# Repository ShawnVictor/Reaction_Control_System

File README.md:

# Reaction_Control_System
This is a repository containing all of the design documents relating to my Reaction Control System (RCS).

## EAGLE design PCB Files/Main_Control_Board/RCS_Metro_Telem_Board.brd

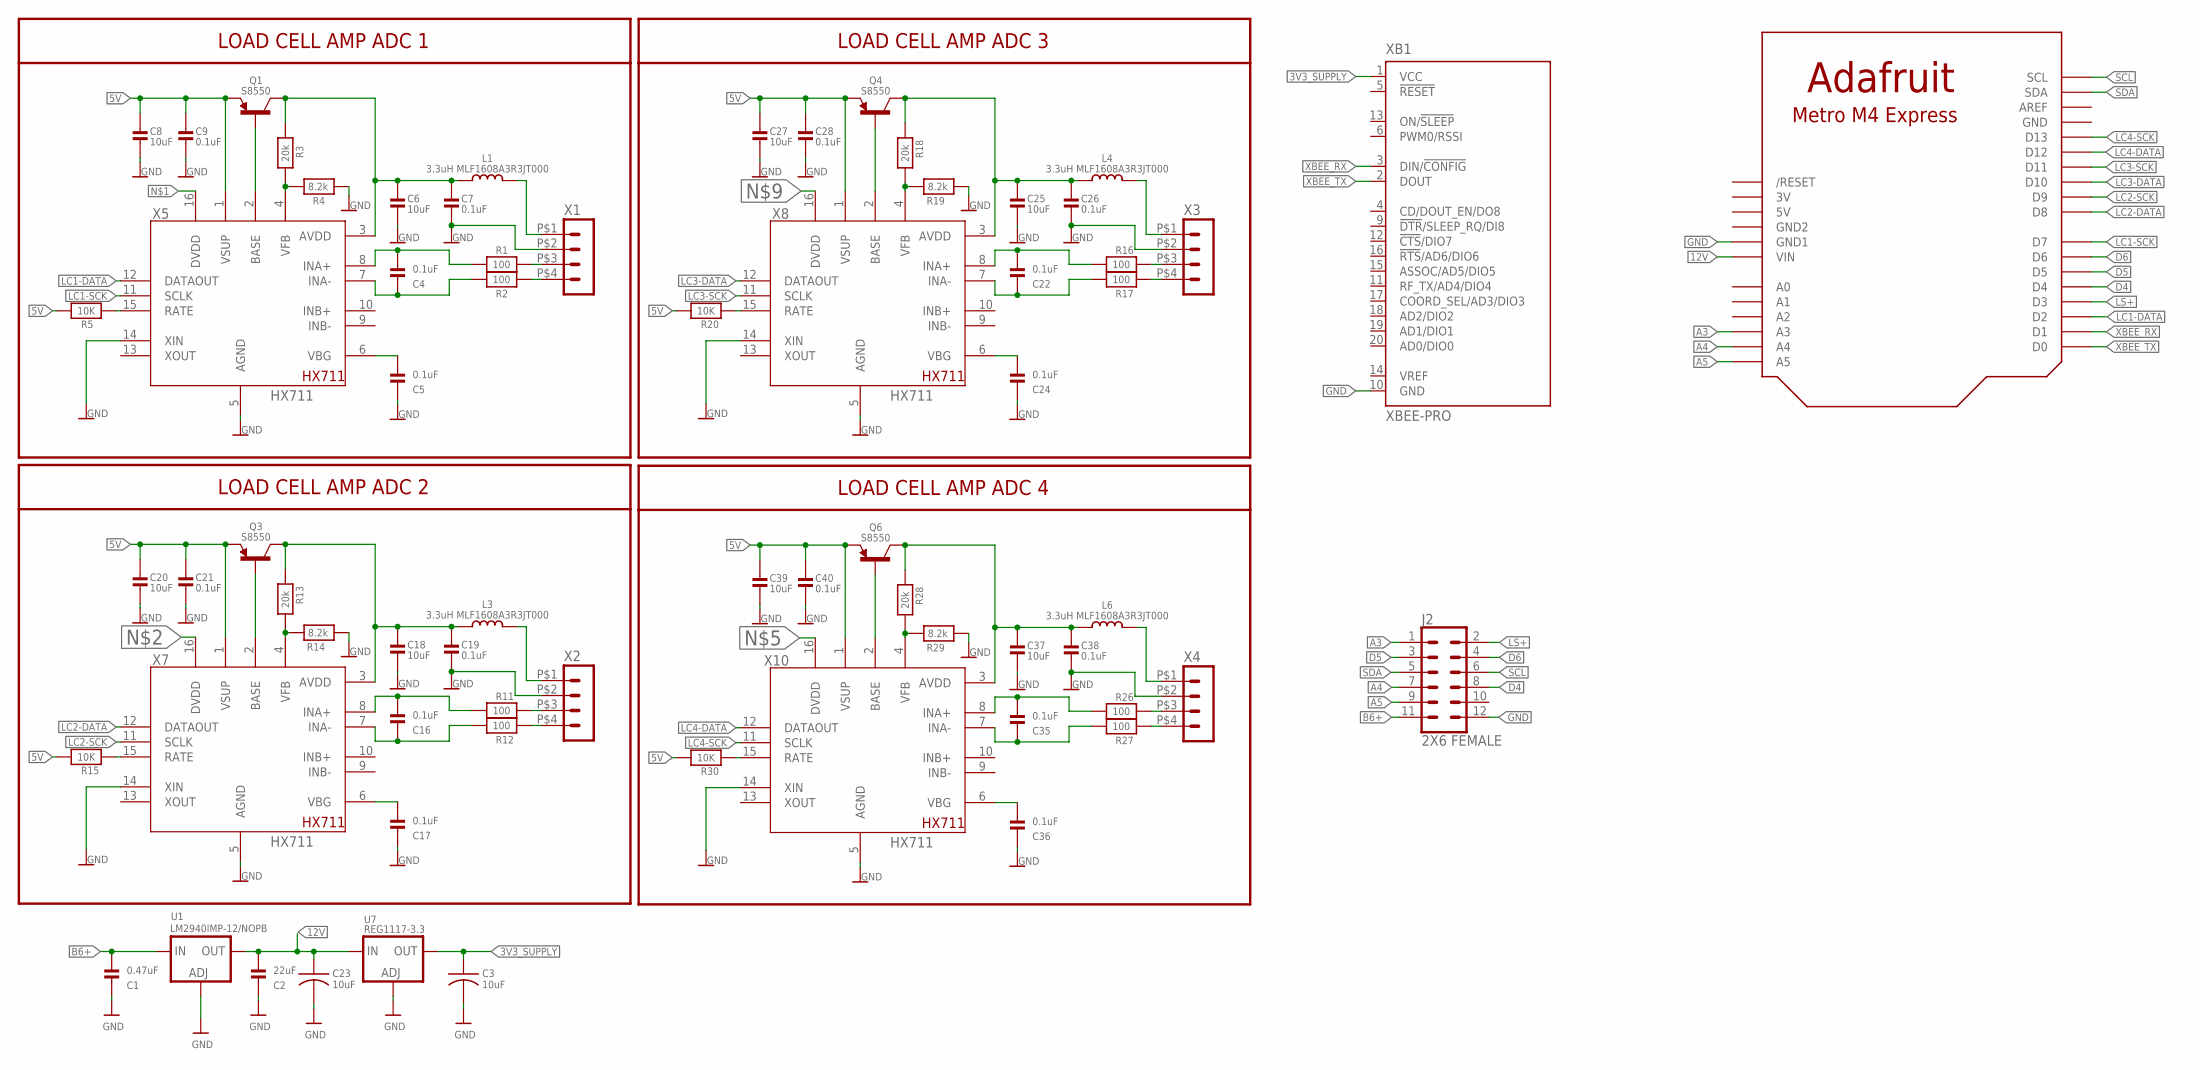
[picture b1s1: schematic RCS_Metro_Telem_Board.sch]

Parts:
C1: 0.47uF; 0603@1
C2: 22uF; 0603@1
C3, C23: 10uF; C0603
C4, C5, C7, C9, C16, C17, C19, C21, C22, C24, C26, C28, C35, C36, C38, C40: 0.1uF; 0603@1
C6, C8, C18, C20, C25, C27, C37, C39: 10uF; 0603@1
J2: 2X6 FEMALE; 2X6
L1, L3, L4, L6: 3.3uH MLF1608A3R3JT000; 0603-NO
Q1, Q3, Q4, Q6: S8550; SOT23-WIDE
R1, R2, R11, R12, R16, R17, R26, R27: 100; 0603@1
R3, R13, R18, R28: 20k; 0603@1
R4, R14, R19, R29: 8.2k; 0603@1
R5, R15, R20, R30: 10K; 0603@1
U1: LM2940IMP-12/NOPB; SOT223-R
U7: REG1117-3.3; SOT223-R
U$1: ADAFRUIT_METRO_M4_EXPRESS
X1, X2, X3, X4: HEADER_POS4_43650-0415; 43650-0415
X5, X7, X8, X10: HX711; SO16
XB1: XBEE-PRO

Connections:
3V: U$1.3V
3V3_SUPPLY: C3.1, U7.2 (OUT), XB1.1 (VCC)
5V: C8.2, C9.2, C20.2, C21.2, C27.2, C28.2, C39.2, C40.2, Q1.2 (E), Q3.2 (E), Q4.2 (E), Q6.2 (E), R5.1, R15.1, R20.1, R30.1, U$1.5V, X5.1 (VSUP), X7.1 (VSUP), X8.1 (VSUP), X10.1 (VSUP)
12V: C2.2, C23.1, U1.2 (OUT), U7.3 (IN), U$1.VIN
A3: J2.1, U$1.A3
A4: J2.7, U$1.A4
A5: J2.9, U$1.A5
B6+: C1.2, J2.11, U1.3 (IN)
D4: J2.8, U$1.D4
D5: J2.3, U$1.D5
D6: J2.4, U$1.D6
GND: C1.1, C2.1, C3.2, C5.1, C6.1, C7.1, C8.1, C9.1, C17.1, C18.1, C19.1, C20.1, C21.1, C23.2, C24.1, C25.1, C26.1, C27.1, C28.1, C36.1, C37.1, C38.1, C39.1, C40.1, J2.12, R4.1, R14.1, R19.1, R29.1, U1.1 (ADJ), U7.1 (ADJ), U$1.GND, U$1.GND1, X1.P$2 (2), X2.P$2 (2), X3.P$2 (2), X4.P$2 (2), X5.5 (AGND), X5.14 (XIN), X7.5 (AGND), X7.14 (XIN), X8.5 (AGND), X8.14 (XIN), X10.5 (AGND), X10.14 (XIN), XB1.10 (GND)
GND2: U$1.GND2
LC1-DATA: U$1.D2, X5.12 (DATAOUT)
LC1-SCK: U$1.D7, X5.11 (SCLK)
LC2-DATA: U$1.D8, X7.12 (DATAOUT)
LC2-SCK: U$1.D9, X7.11 (SCLK)
LC3-DATA: U$1.D10, X8.12 (DATAOUT)
LC3-SCK: U$1.D11, X8.11 (SCLK)
LC4-DATA: U$1.D12, X10.12 (DATAOUT)
LC4-SCK: U$1.D13, X10.11 (SCLK)
LS+: J2.2, U$1.D3
unnamed: R1.2, X1.P$3 (3)
unnamed: R2.2, X1.P$4 (4)
unnamed: C4.1, R2.1, X5.7 (INA-)
unnamed: C4.2, R1.1, X5.8 (INA+)
unnamed: C5.2, X5.6 (VBG)
unnamed: L1.2, X1.P$1 (1)
unnamed: R3.1, R4.2, X5.4 (VFB)
unnamed: Q1.1 (B), X5.2 (BASE)
unnamed: C6.2, C7.2, L1.1, Q1.3 (C), R3.2, X5.3 (AVDD)
unnamed: R5.2, X5.15 (RATE)
unnamed: R11.2, X2.P$3 (3)
unnamed: R12.2, X2.P$4 (4)
unnamed: C16.1, R12.1, X7.7 (INA-)
unnamed: C16.2, R11.1, X7.8 (INA+)
unnamed: C17.2, X7.6 (VBG)
unnamed: L3.2, X2.P$1 (1)
unnamed: R13.1, R14.2, X7.4 (VFB)
unnamed: Q3.1 (B), X7.2 (BASE)
unnamed: C18.2, C19.2, L3.1, Q3.3 (C), R13.2, X7.3 (AVDD)
unnamed: R15.2, X7.15 (RATE)
unnamed: R16.2, X3.P$3 (3)
unnamed: R17.2, X3.P$4 (4)
unnamed: C22.1, R17.1, X8.7 (INA-)
unnamed: C22.2, R16.1, X8.8 (INA+)
unnamed: C24.2, X8.6 (VBG)
unnamed: L4.2, X3.P$1 (1)
unnamed: R18.1, R19.2, X8.4 (VFB)
unnamed: Q4.1 (B), X8.2 (BASE)
unnamed: C25.2, C26.2, L4.1, Q4.3 (C), R18.2, X8.3 (AVDD)
unnamed: R20.2, X8.15 (RATE)
unnamed: R26.2, X4.P$3 (3)
unnamed: R27.2, X4.P$4 (4)
unnamed: C35.1, R27.1, X10.7 (INA-)
unnamed: C35.2, R26.1, X10.8 (INA+)
unnamed: C36.2, X10.6 (VBG)
unnamed: L6.2, X4.P$1 (1)
unnamed: R28.1, R29.2, X10.4 (VFB)
unnamed: Q6.1 (B), X10.2 (BASE)
unnamed: C37.2, C38.2, L6.1, Q6.3 (C), R28.2, X10.3 (AVDD)
unnamed: R30.2, X10.15 (RATE)
SCL: J2.6, U$1.SCL
SDA: J2.5, U$1.SDA
XBEE_RX: U$1.D1, XB1.3 (DIN/!CONFIG)
XBEE_TX: U$1.D0, XB1.2 (DOUT)

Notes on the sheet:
LOAD CELL AMP ADC 1
LOAD CELL AMP ADC 2
LOAD CELL AMP ADC 3
LOAD CELL AMP ADC 4

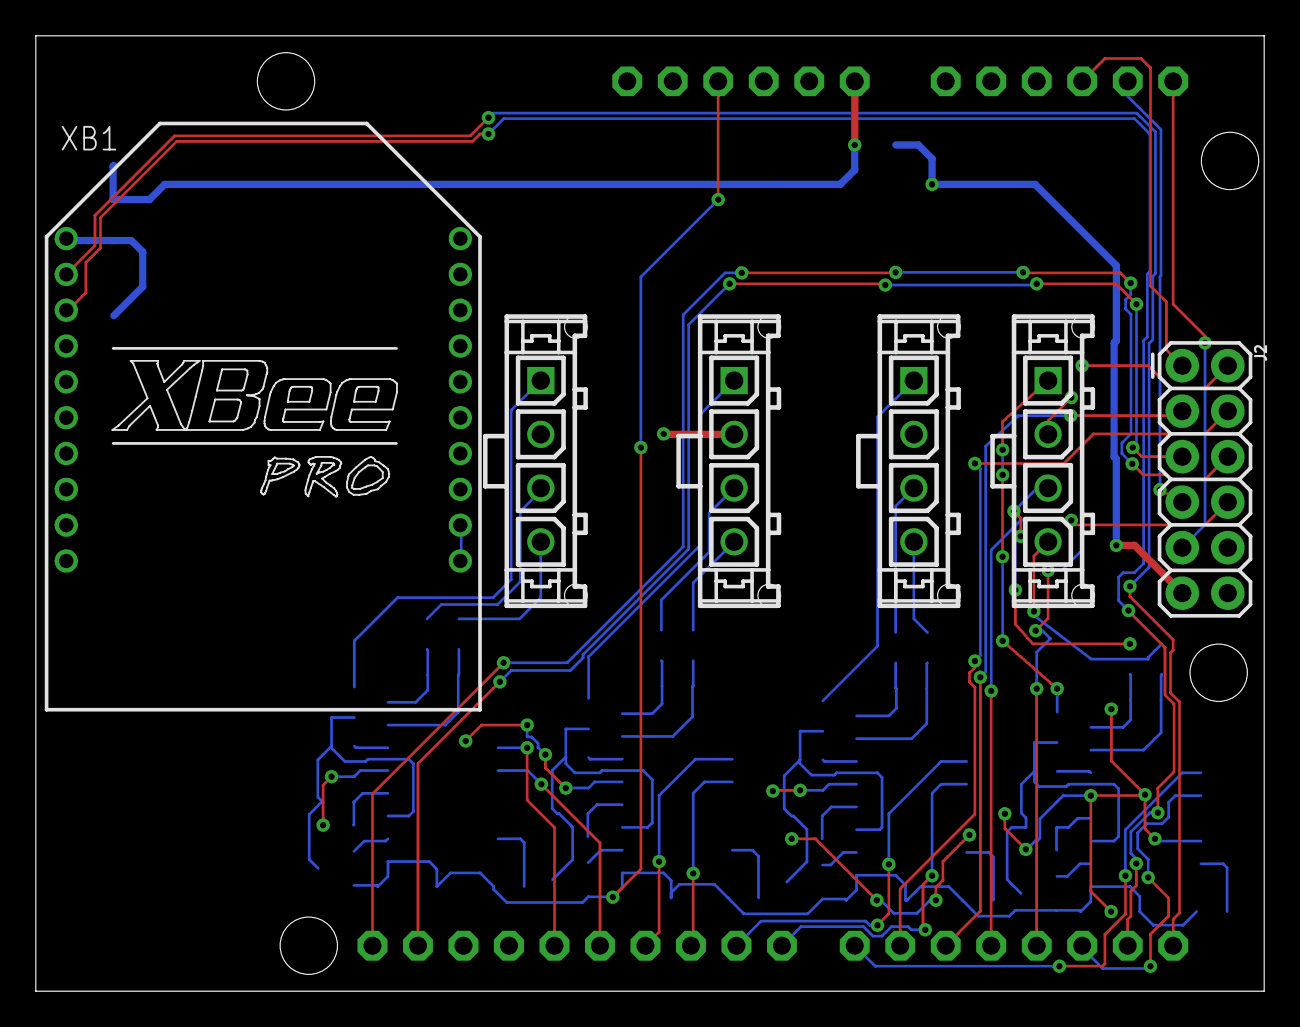
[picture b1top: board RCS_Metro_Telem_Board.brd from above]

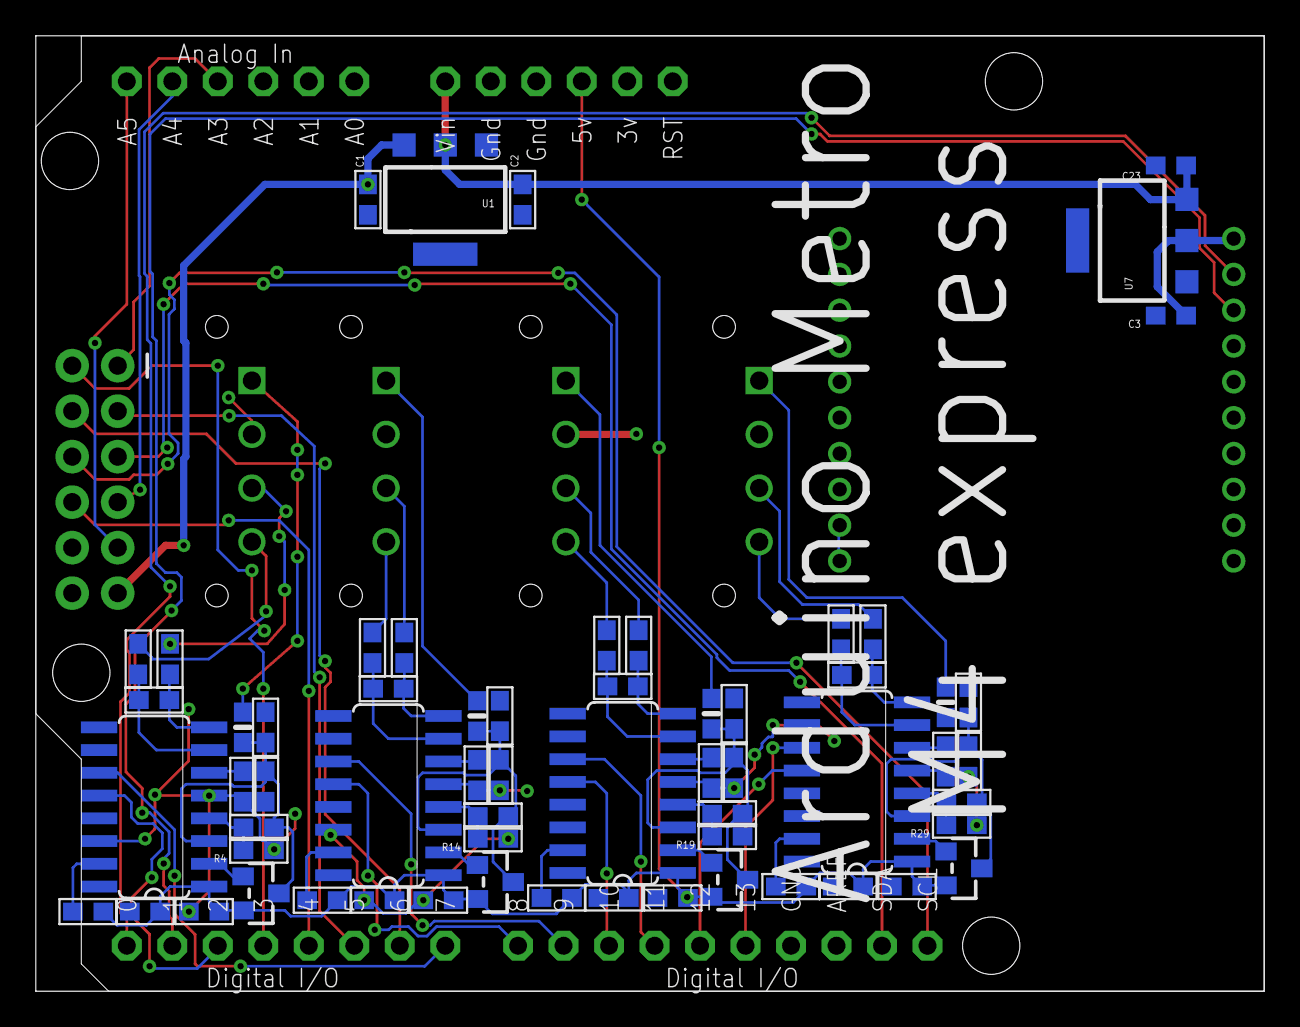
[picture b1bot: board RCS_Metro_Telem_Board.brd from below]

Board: 2 copper layers, 68.6 x 53.3 mm, 69 parts (63 on the bottom side), 64 nets.

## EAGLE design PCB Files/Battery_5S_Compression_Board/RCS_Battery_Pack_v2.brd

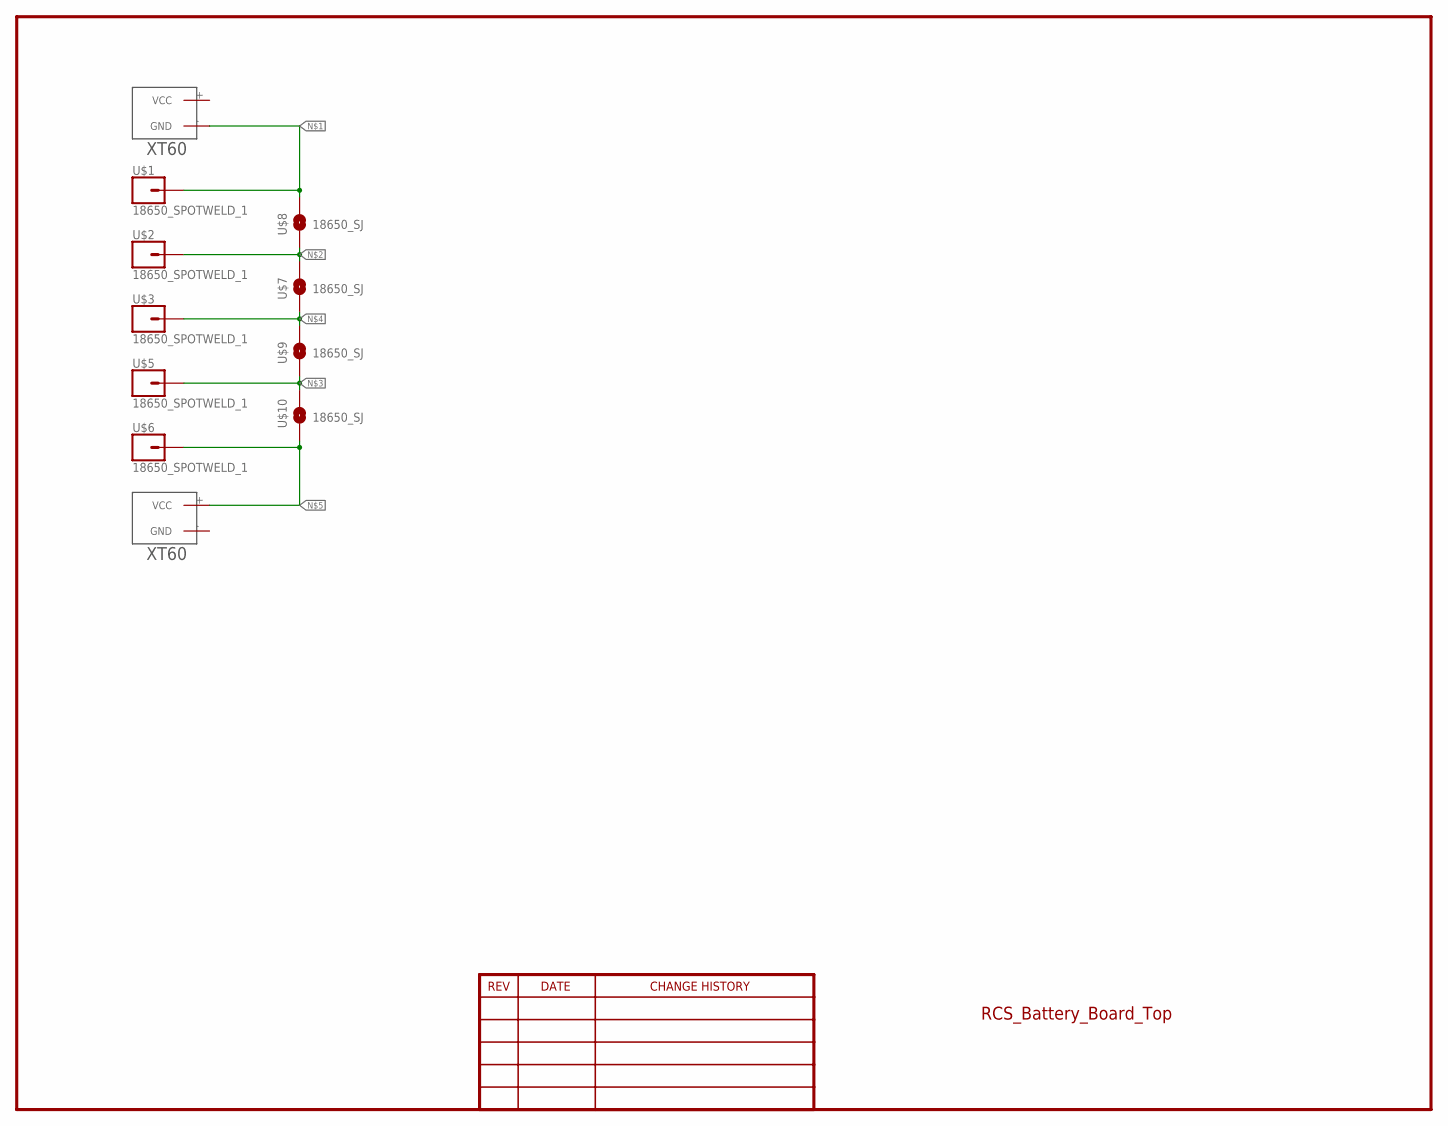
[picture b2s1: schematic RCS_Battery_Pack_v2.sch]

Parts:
U$1, U$2, U$3, U$5, U$6: 18650_SPOTWELD_1
U$4, U$11: XT60
U$7, U$8, U$9, U$10: 18650_SJ; SJ_2S-NO

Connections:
unnamed: U$1.1, U$4.- (GND), U$8.2
unnamed: U$2.1, U$7.2, U$8.1
unnamed: U$5.1, U$9.1, U$10.2
unnamed: U$3.1, U$7.1, U$9.2
unnamed: U$6.1, U$10.1, U$11.+ (VCC)

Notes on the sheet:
RCS_Battery_Board_Top

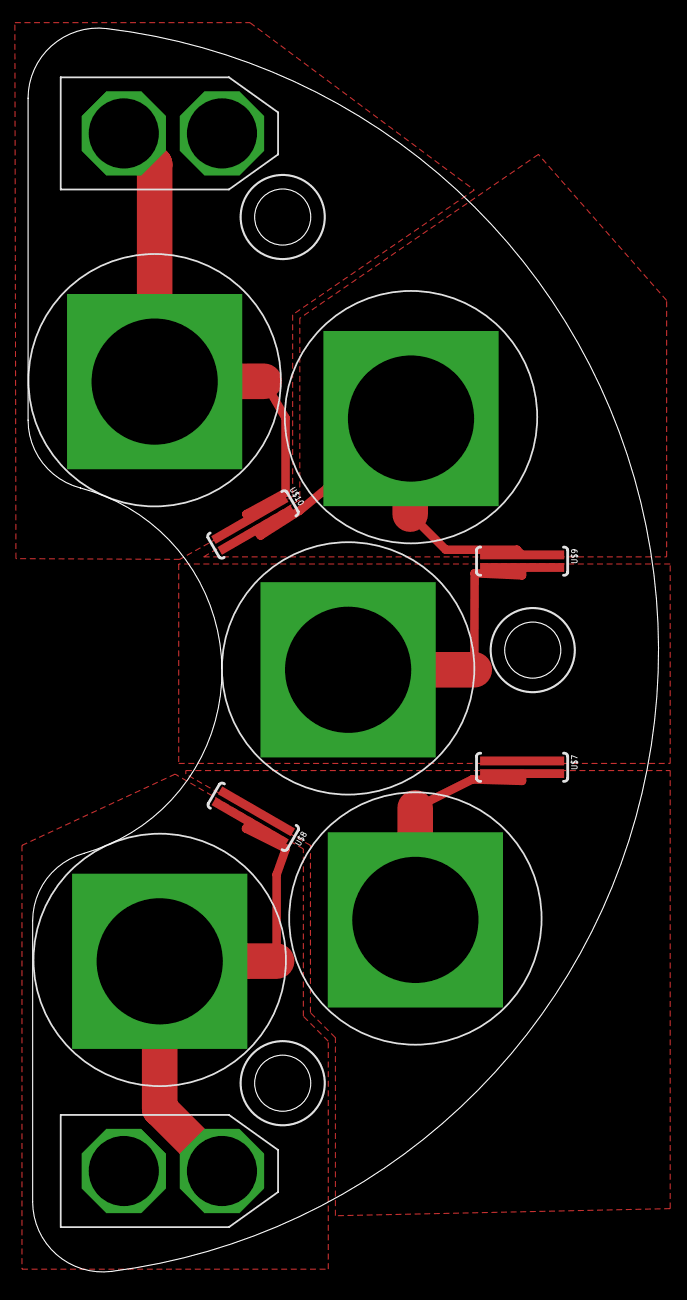
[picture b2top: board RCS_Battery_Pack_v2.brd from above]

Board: 2 copper layers, 45.0 x 88.7 mm, 11 parts (0 on the bottom side), 5 nets.

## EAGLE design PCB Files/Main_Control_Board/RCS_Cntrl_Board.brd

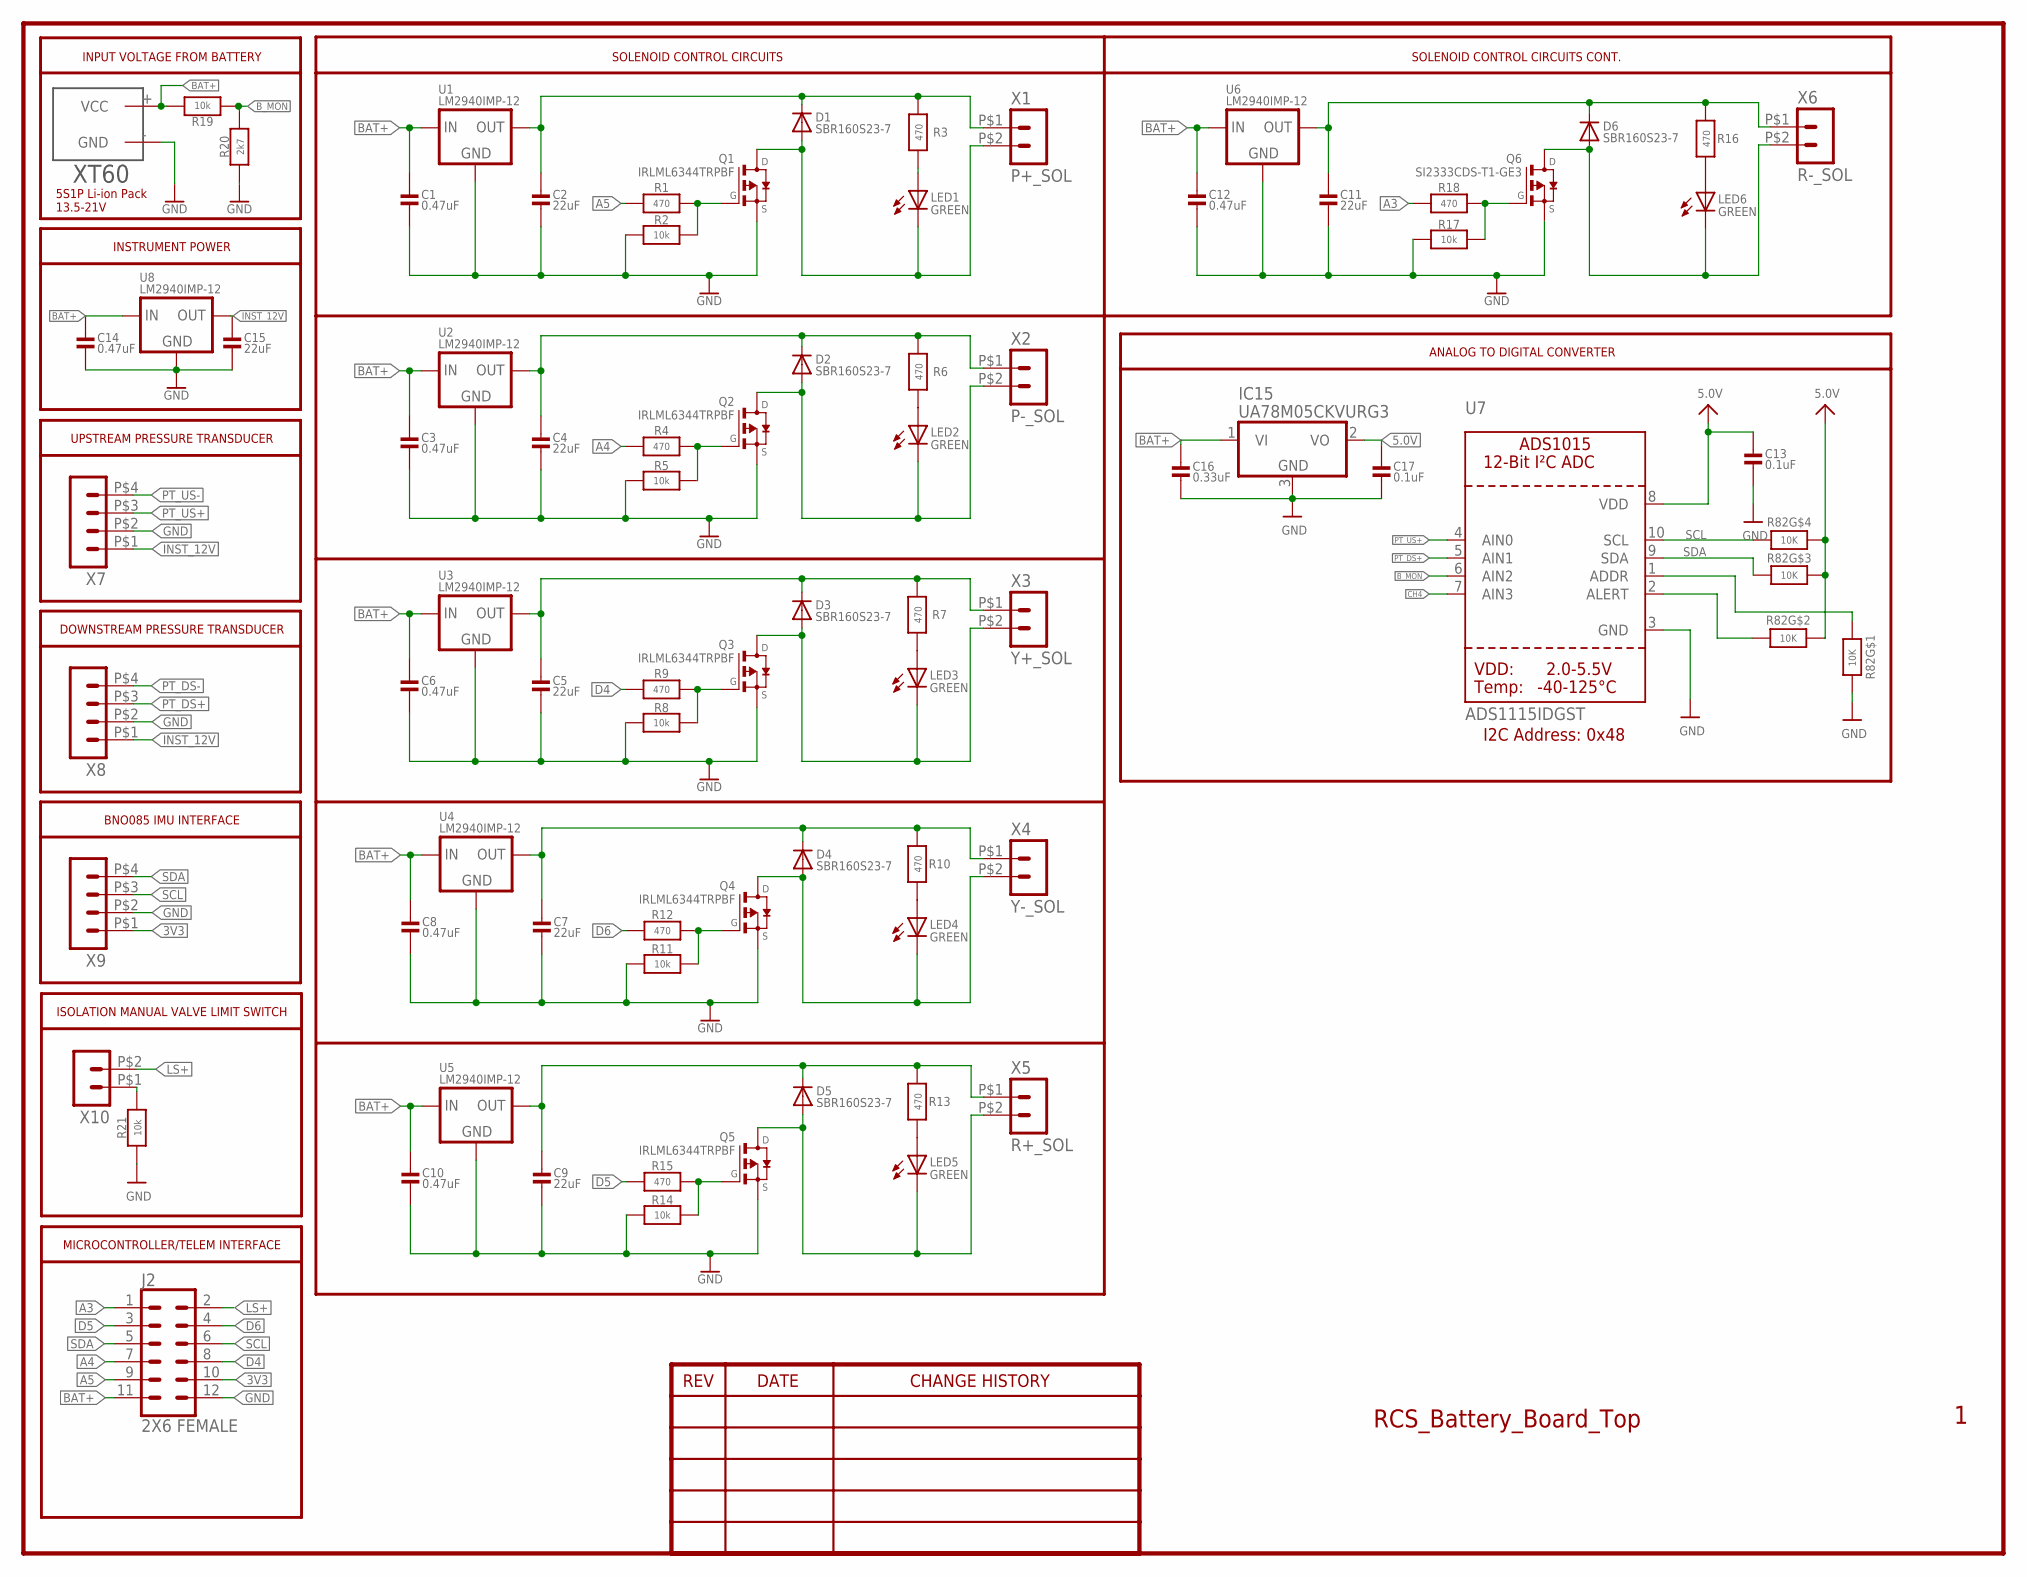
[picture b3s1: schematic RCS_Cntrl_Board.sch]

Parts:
C1, C3, C6, C8, C10, C12, C14: 0.47uF; 0603
C2, C4, C5, C7, C9, C11, C15: 22uF; 0603
C13, C17: 0.1uF; 0603
C16: 0.33uF; 0603
D1, D2, D3, D4, D5, D6: SBR160S23-7; SOT23-R
IC15: UA78M05CKVURG3; TO252
J2: 2X6 FEMALE; 2X6
LED1, LED2, LED3, LED4, LED5, LED6: GREEN; CHIPLED_0603
Q1, Q2, Q3, Q4, Q5: IRLML6344TRPBF; TRANSISTOR-FET_SOT23
Q6: SI2333CDS-T1-GE3; TRANSISTOR-FET_SOT23
R1, R3, R4, R6, R7, R9, R10, R12, R13, R15, R16, R18: 470; 0603-NO
R2, R5, R8, R11, R14, R17, R19, R21: 10k; 0603-NO
R20: 2k7; 0603-NO
R82: 10K; RESPACK_4X0603
U1, U2, U3, U4, U5, U6, U8: LM2940IMP-12; SOT223-R
U7: ADS1115IDGST; MSOP10
U$4: XT60
X1: P+_SOL; 44914-0201
X2: P-_SOL; 44914-0201
X3: Y+_SOL; 44914-0201
X4: Y-_SOL; 44914-0201
X5: R+_SOL; 44914-0201
X6: R-_SOL; 44914-0201
X7, X8, X9: HEADER_POS4_43650-0415; 43650-0415
X10: HEADER_POS2_43650-0215; 43650-0215

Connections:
3V3: J2.10, X9.P$1 (1)
5.0V: C13.2, C17.2, IC15.2 (VO), R82.5 (2), R82.6 (2), R82.7 (2), U7.8 (VDD)
A3: J2.1, R18.1
A4: J2.7, R4.1
A5: J2.9, R1.1
BAT+: C1.2, C3.2, C6.2, C8.2, C10.2, C12.2, C14.2, C16.2, IC15.1 (VI), J2.11, R19.2, U1.1 (IN), U2.1 (IN), U3.1 (IN), U4.1 (IN), U5.1 (IN), U6.1 (IN), U8.1 (IN), U$4.+ (VCC)
B_MON: R19.1, R20.2, U7.6 (AIN2)
CH4: U7.7 (AIN3)
D4: J2.8, R9.1
D5: J2.3, R15.1
D6: J2.4, R12.1
GND: C1.1, C2.1, C3.1, C4.1, C5.1, C6.1, C7.1, C8.1, C9.1, C10.1, C11.1, C12.1, C13.1, C14.1, C15.1, C16.1, C17.1, IC15.3 (GND), J2.12, Q1.2 (S), Q2.2 (S), Q3.2 (S), Q4.2 (S), Q5.2 (S), Q6.2 (S), R2.1, R5.1, R8.1, R11.1, R14.1, R17.1, R20.1, R21.1, R82.8 (2), U1.2 (GND), U2.2 (GND), U3.2 (GND), U4.2 (GND), U5.2 (GND), U6.2 (GND), U7.3 (GND), U8.2 (GND), U$4.- (GND), X7.P$2 (2), X8.P$2 (2), X9.P$2 (2)
INST_12V: C15.2, U8.3 (OUT), X7.P$1 (1), X8.P$1 (1)
LS+: J2.2, X10.P$2 (2)
unnamed: LED1.A, R3.1
unnamed: C2.2, D1.3 (C), R3.2, U1.3 (OUT), X1.P$1 (1)
unnamed: D2.1 (A), LED2.C, Q2.3 (D), X2.P$2 (2)
unnamed: LED2.A, R6.1
unnamed: Q2.1 (G), R4.2, R5.2
unnamed: D3.1 (A), LED3.C, Q3.3 (D), X3.P$2 (2)
unnamed: Q3.1 (G), R8.2, R9.2
unnamed: C4.2, D2.3 (C), R6.2, U2.3 (OUT), X2.P$1 (1)
unnamed: LED3.A, R7.1
unnamed: D4.1 (A), LED4.C, Q4.3 (D), X4.P$2 (2)
unnamed: D5.1 (A), LED5.C, Q5.3 (D), X5.P$2 (2)
unnamed: C5.2, D3.3 (C), R7.2, U3.3 (OUT), X3.P$1 (1)
unnamed: LED4.A, R10.1
unnamed: Q4.1 (G), R11.2, R12.2
unnamed: C7.2, D4.3 (C), R10.2, U4.3 (OUT), X4.P$1 (1)
unnamed: Q5.1 (G), R14.2, R15.2
unnamed: LED5.A, R13.1
unnamed: D6.1 (A), LED6.C, Q6.3 (D), X6.P$2 (2)
unnamed: Q6.1 (G), R17.2, R18.2
unnamed: C9.2, D5.3 (C), R13.2, U5.3 (OUT), X5.P$1 (1)
unnamed: LED6.A, R16.1
unnamed: C11.2, D6.3 (C), R16.2, U6.3 (OUT), X6.P$1 (1)
unnamed: R21.2, X10.P$1 (1)
unnamed: D1.1 (A), LED1.C, Q1.3 (D), X1.P$2 (2)
unnamed: Q1.1 (G), R1.2, R2.2
unnamed: R82.2 (1), U7.2 (ALERT)
unnamed: R82.1, U7.1 (ADDR)
PT_DS+: U7.5 (AIN1), X8.P$3 (3)
PT_DS-: X8.P$4 (4)
PT_US+: U7.4 (AIN0), X7.P$3 (3)
PT_US-: X7.P$4 (4)
SCL: J2.6, R82.4 (1), U7.10 (SCL), X9.P$3 (3)
SDA: J2.5, R82.3 (1), U7.9 (SDA), X9.P$4 (4)

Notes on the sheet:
RCS_Battery_Board_Top
INPUT VOLTAGE FROM BATTERY
5S1P Li-ion Pack
13.5-21V
SOLENOID CONTROL CIRCUITS
SOLENOID CONTROL CIRCUITS CONT.
ANALOG TO DIGITAL CONVERTER
I2C Address: 0x48
UPSTREAM PRESSURE TRANSDUCER
DOWNSTREAM PRESSURE TRANSDUCER
INSTRUMENT POWER
BNO085 IMU INTERFACE
ISOLATION MANUAL VALVE LIMIT SWITCH
MICROCONTROLLER/TELEM INTERFACE

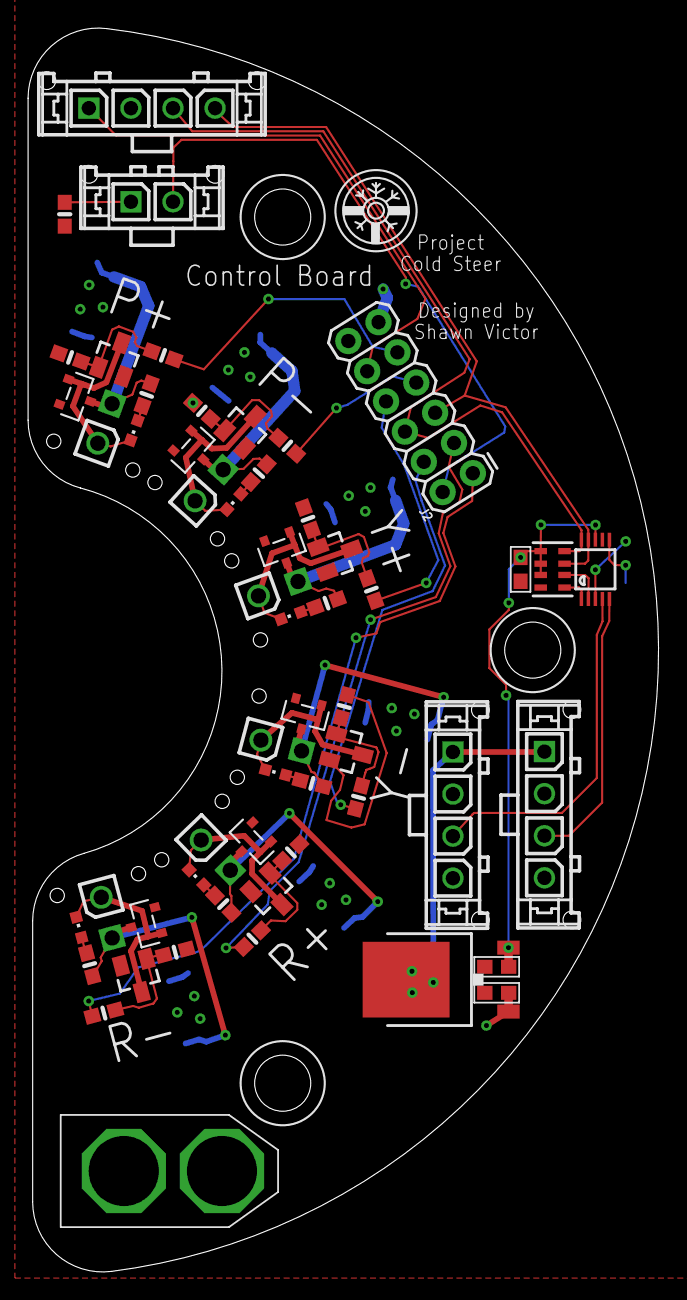
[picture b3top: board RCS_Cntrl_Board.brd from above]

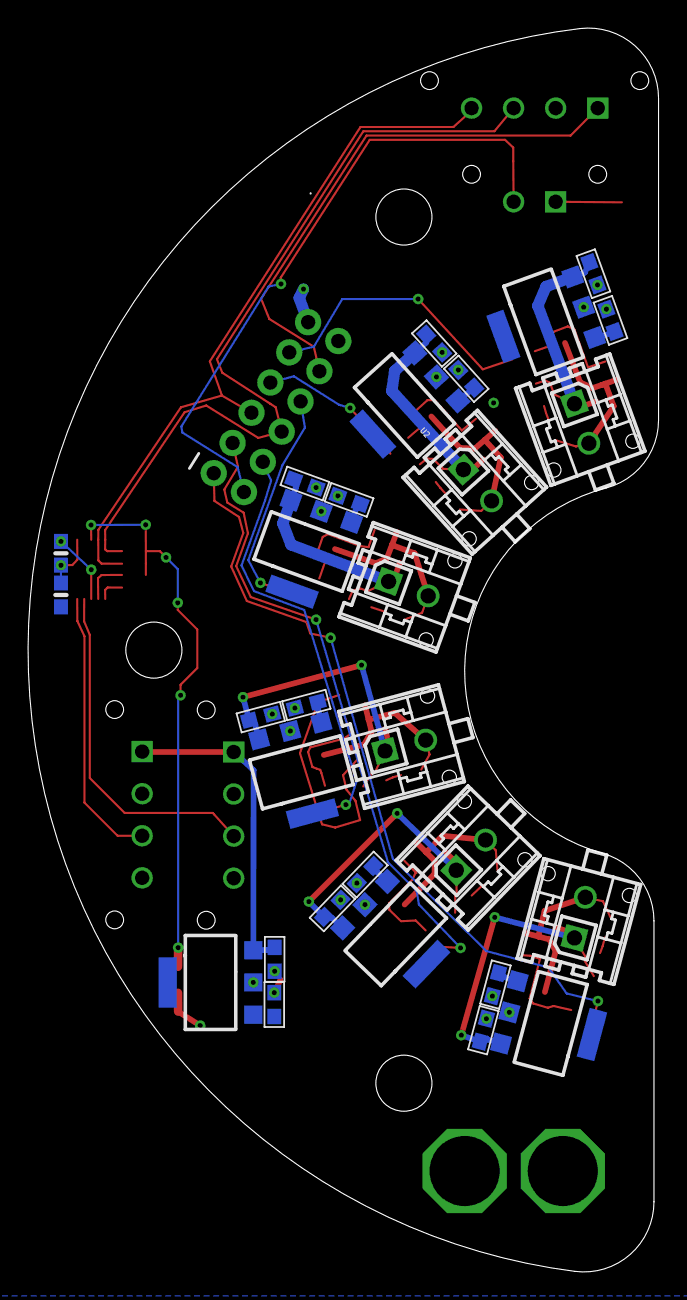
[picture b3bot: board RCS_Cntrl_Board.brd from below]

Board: 2 copper layers, 45.0 x 88.7 mm, 78 parts (29 on the bottom side), 44 nets.

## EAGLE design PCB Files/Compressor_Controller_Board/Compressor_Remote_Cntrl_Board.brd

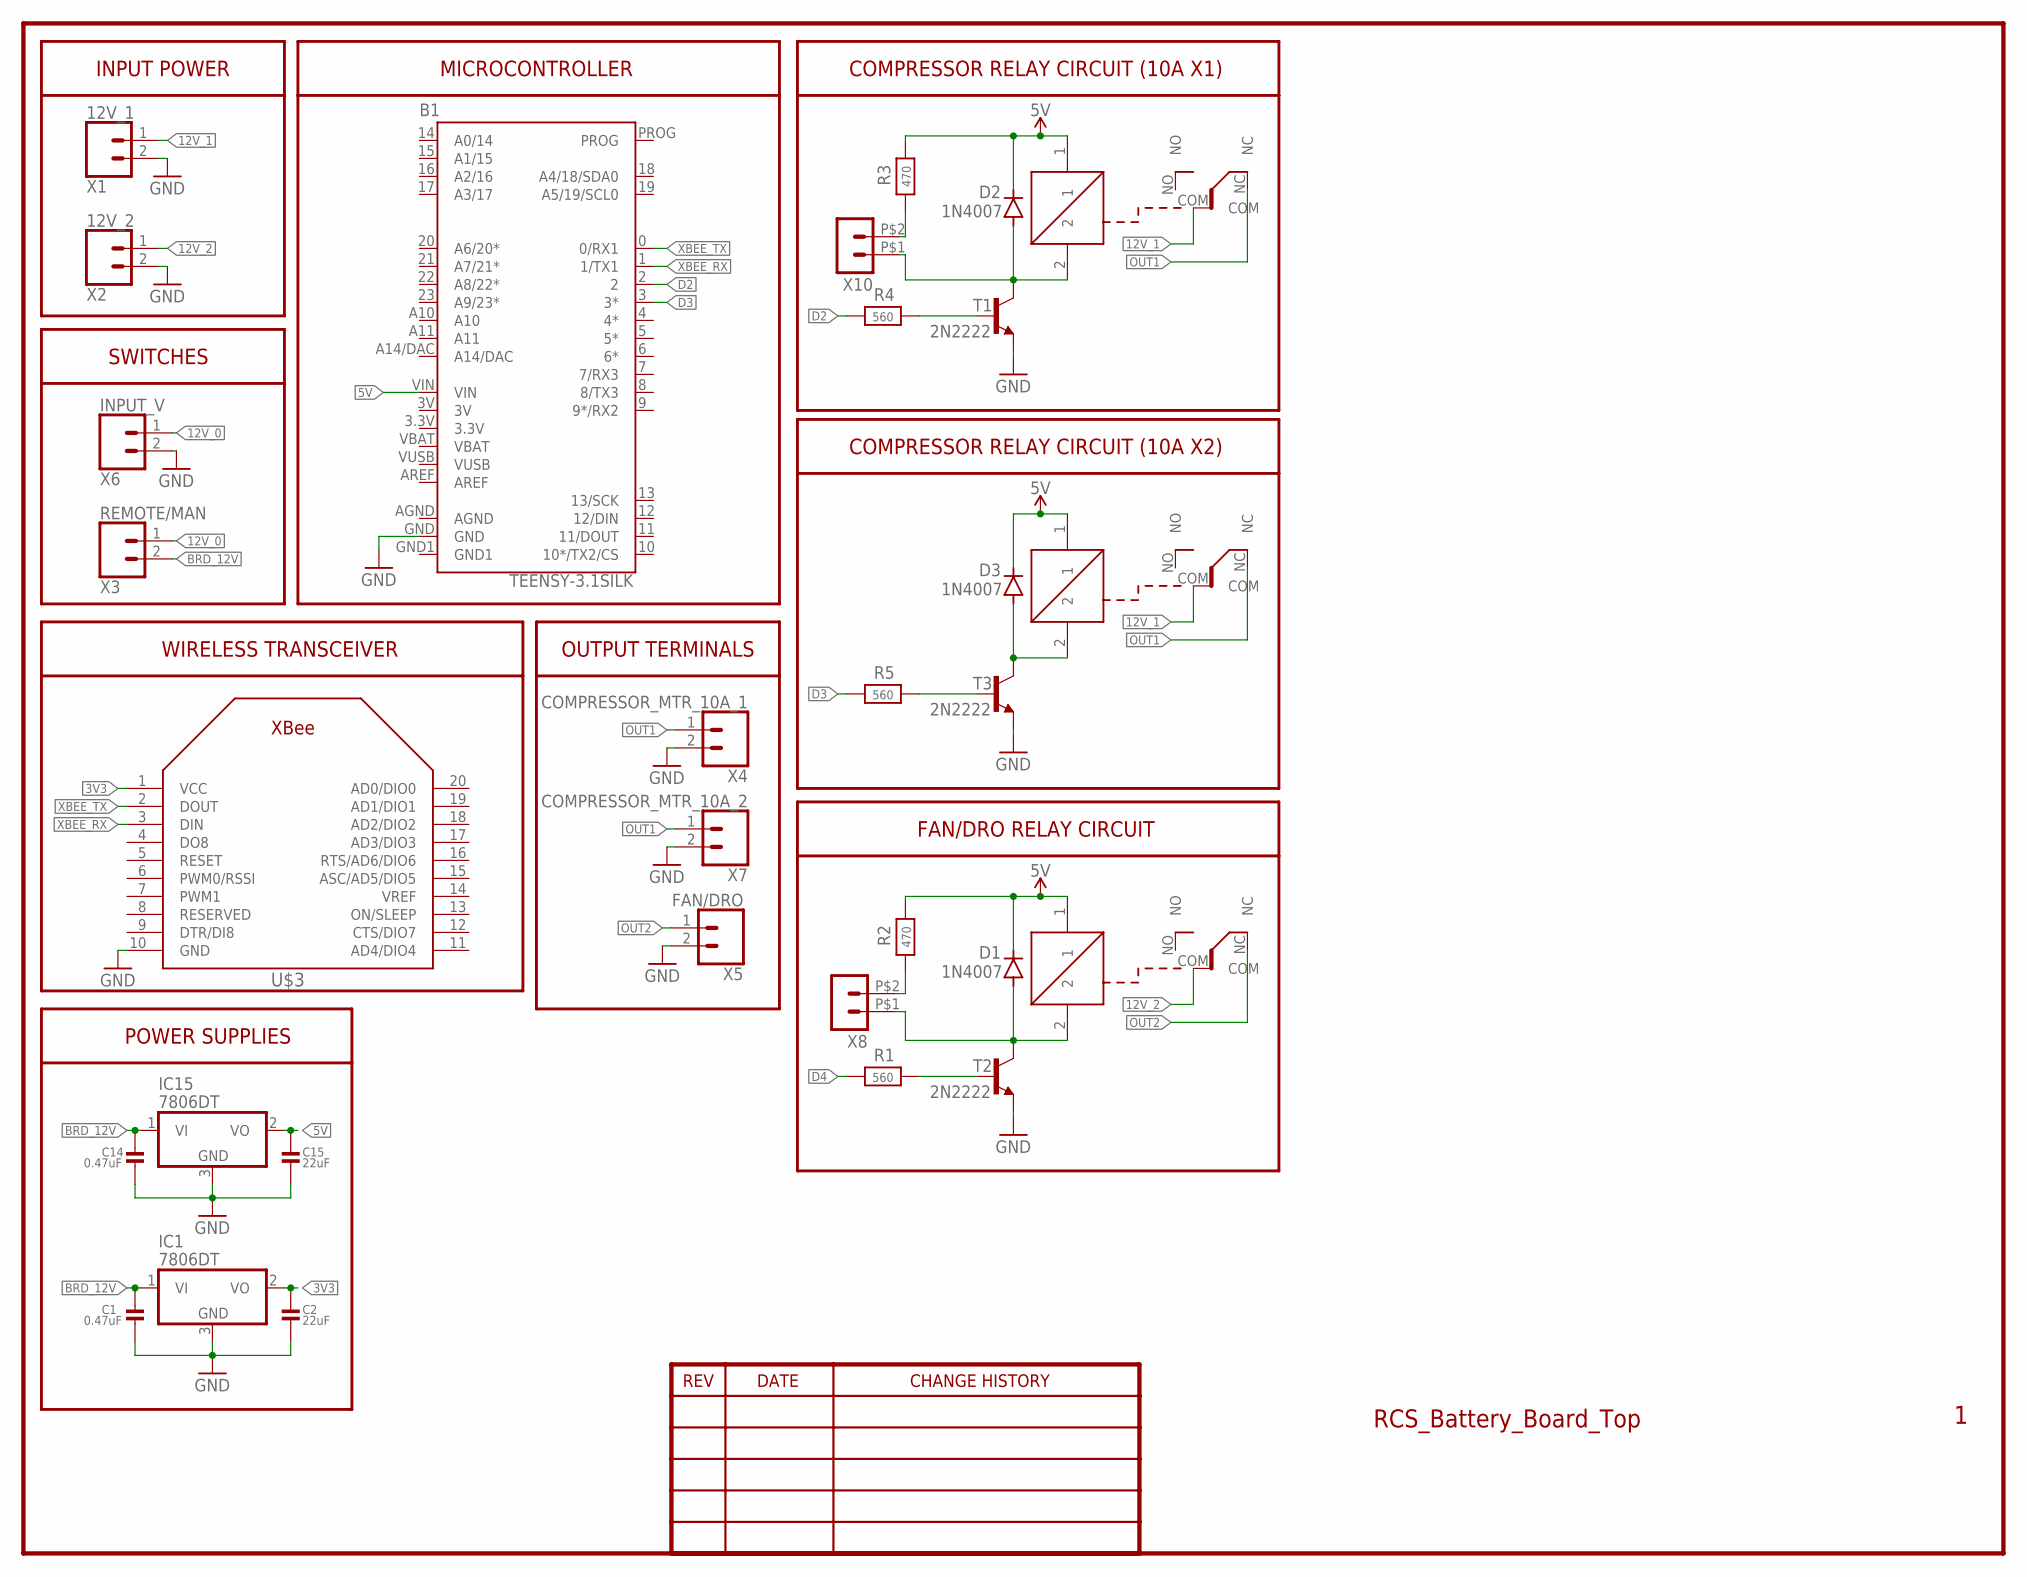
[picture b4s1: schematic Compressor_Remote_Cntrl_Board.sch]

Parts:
B1: TEENSY-3.1SILK; TEENSY-3.1
C1, C14: 0.47uF; 0603
C2, C15: 22uF; 0603
D1, D2, D3: 1N4007; DO-41
IC1, IC15: 7806DT; TO252
R1, R4, R5: 560; 0805
R2, R3: 470; 0805
T1, T2, T3: 2N2222; TO92-EBC-OVAL
U$1, U$2, U$4: RW-SH
U$3: XBEE
X1: 12V_1; SCREWTERMINAL-5MM-2
X2: 12V_2; SCREWTERMINAL-5MM-2
X3: REMOTE/MAN; SCREWTERMINAL-5MM-2
X4: COMPRESSOR_MTR_10A_1; SCREWTERMINAL-5MM-2
X5: FAN/DRO; SCREWTERMINAL-5MM-2
X6: INPUT_V; SCREWTERMINAL-5MM-2
X7: COMPRESSOR_MTR_10A_2; SCREWTERMINAL-5MM-2
X8, X10: HEADER_POS2_43650-0215; 43650-0215

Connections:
3.3V: B1.3.3V
3V: B1.3V
3V3: C2.2, IC1.2 (VO), U$3.1 (VCC)
5V: B1.VIN, C15.2, D1.C, D2.C, D3.C, IC15.2 (VO), R2.2, R3.2, U$1.1, U$2.1, U$4.1
12V_0: X3.1, X6.1
12V_1: U$2.COM, U$4.COM, X1.1
12V_2: U$1.COM, X2.1
AGND: B1.AGND
BRD_12V: C1.2, C14.2, IC1.1 (VI), IC15.1 (VI), X3.2
D2: B1.2, R4.1
D3: B1.3 (3*), R5.1
D4: R1.1
GND: B1.GND, C1.1, C2.1, C14.1, C15.1, IC1.3 (GND), IC15.3 (GND), T1.E, T2.E, T3.E, U$3.10 (GND), X1.2, X2.2, X4.2, X5.2, X6.2, X7.2
GND1: B1.GND1
unnamed: D1.A, T2.C, U$1.2, X8.P$1 (1)
unnamed: R1.2, T2.B
unnamed: R2.1, X8.P$2 (2)
unnamed: D3.A, T3.C, U$4.2
unnamed: R5.2, T3.B
unnamed: R4.2, T1.B
unnamed: D2.A, T1.C, U$2.2, X10.P$1 (1)
unnamed: R3.1, X10.P$2 (2)
OUT1: U$2.NC, U$4.NC, X4.1, X7.1
OUT2: U$1.NC, X5.1
VBAT: B1.VBAT
VUSB: B1.VUSB
XBEE_RX: B1.1 (1/TX1), U$3.3 (DIN)
XBEE_TX: B1.0 (0/RX1), U$3.2 (DOUT)

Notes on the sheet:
RCS_Battery_Board_Top
INPUT POWER
SWITCHES
COMPRESSOR RELAY CIRCUIT (10A X1)
FAN/DRO RELAY CIRCUIT
OUTPUT TERMINALS
MICROCONTROLLER
POWER SUPPLIES
WIRELESS TRANSCEIVER
COMPRESSOR RELAY CIRCUIT (10A X2)

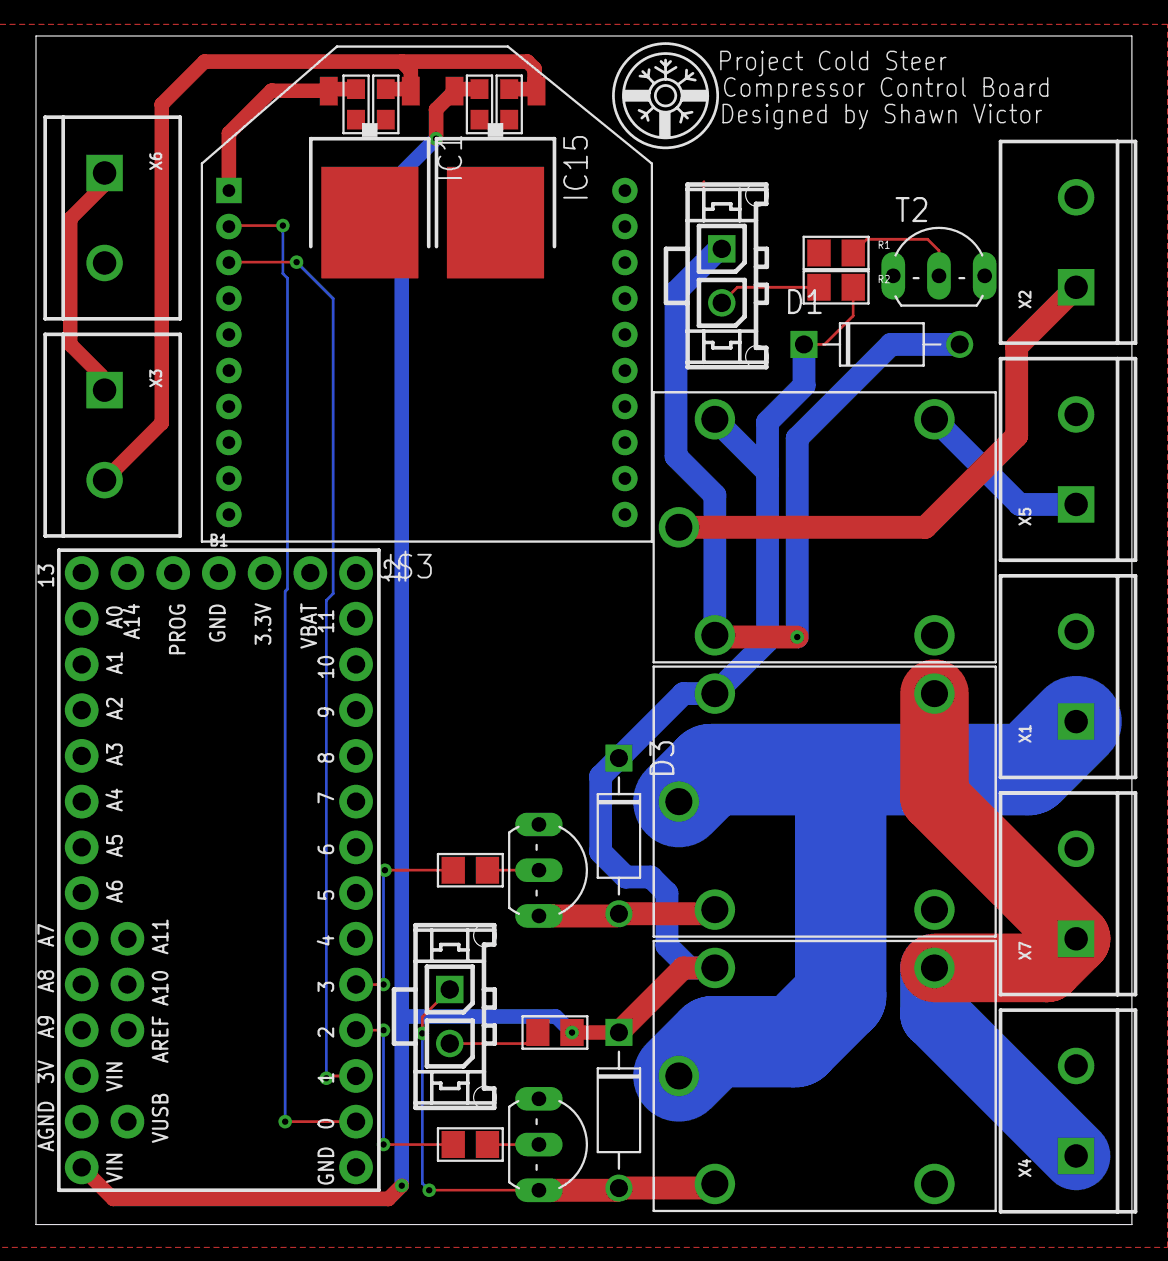
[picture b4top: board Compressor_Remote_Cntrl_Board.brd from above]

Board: 2 copper layers, 60.9 x 66.0 mm, 31 parts (0 on the bottom side), 21 nets.

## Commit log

2024-12-17 Initial Codebase Commit
2024-12-17 Added PCB Files for Metro Shield Board
2024-12-30 Modified File Structure, Created RCS Main Controller Code, Working Telem on Serial Monitor
2024-12-30 Processing Code now runs, but has bugs
2024-12-30 Plotting Works now, reading in US/DS Pressure
2024-12-31 Processing GUI working with live sensor plots/watchdogs
2024-12-31 Added event handling for toggle switching
2024-12-31 Logging Functionality works
2024-12-31 fixed issue where datapackets were 16bit and LC data was wrapping around
2025-01-02 Working GUI with scaled lc2
2025-01-05 Added Code for TX/RX functionality & Valve Commandability
2025-01-05 Working Version w/ Valve Commandability.
2025-01-17 Updated Quaternion Receiver to update newest Packet Structure

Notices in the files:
parts and their libraries:
dframes: Copyright (C) 2004, Bob Starr (bobstarr@mindspring.com)
SparkFun-Connectors: Licensing: Creative Commons ShareAlike 4.0 International - https://creativecommons.org/licenses/by-sa/4.0
